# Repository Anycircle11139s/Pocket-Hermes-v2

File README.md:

# Pocket-Hermes-v2
I created a custom device which senses and displays the temperature. It is powered by a xiao esp32-s3, so it can connect to wifi/bluetooth. This can be used to fetch apis like time or bus times. I added a rotary encoder for navigation and designed it to be as compact as possible. I made the PCB black with slick af silkscreen and it is powered by a small lipo battery.

<br>

BOM: 
<br>

128 x 64 OLED display
<br>

EC11 Rotary Encoder
<br>

4.7k resistors (3)
<br>

3.7v Lipo Battery
<br>

XIAO ESP32 S3 Microcontroller
<br>

PCB
<br>

Assembly instructions:
<br>
Start by soldering all the components onto the pcb (microcontroller, OLED dislpay, temperature sensor, etc)
<br>
Next, solder the Lipo battery to the microcontroller and carefully place it in the case's slot. 
<br>
After that, screw the lid down with the m2 screws.
3D printed case from Printing Legion<br>

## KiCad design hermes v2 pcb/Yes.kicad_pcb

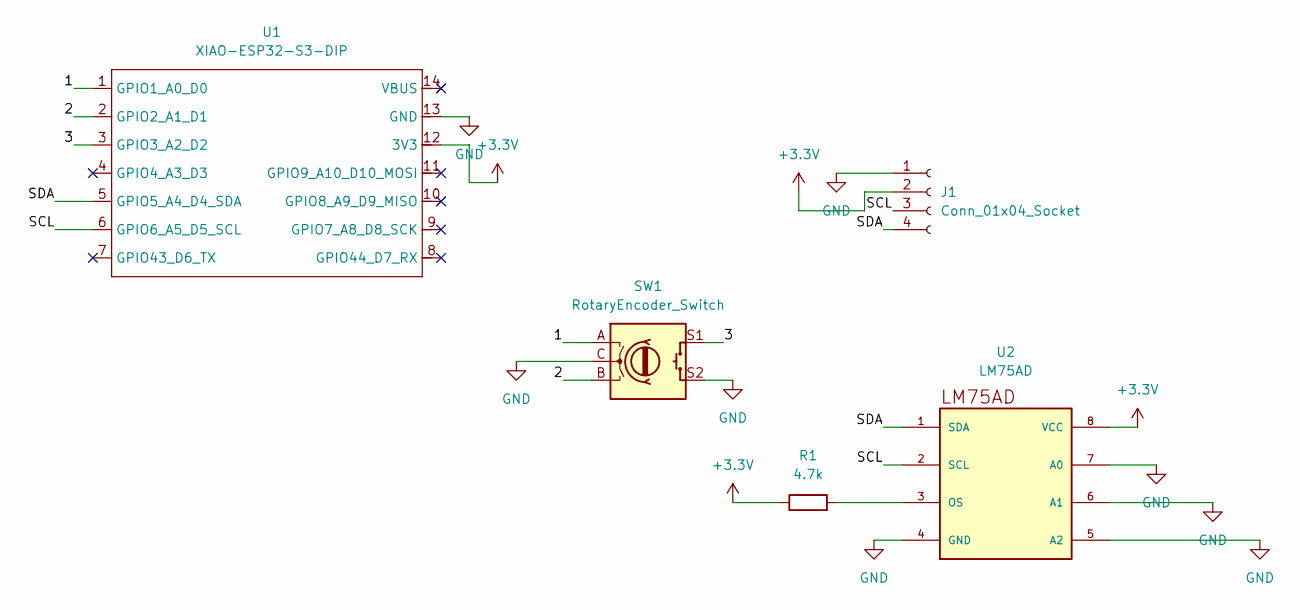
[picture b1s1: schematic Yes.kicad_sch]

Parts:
J1: Conn_01x04_Socket; PinHeader_1x04_P2.54mm_Vertical
R1: 4.7k; R_Axial_DIN0207_L6.3mm_D2.5mm_P7.62mm_Horizontal
SW1: RotaryEncoder_Switch; RotaryEncoder_Alps_EC11E-Switch_Vertical_H20mm
U1: XIAO-ESP32-S3-DIP
U2: LM75AD; SOIC-8

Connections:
+3.3V: J1.2, R1.1, U1.12 (3V3), U2.8 (VCC)
/1: SW1.A, U1.1 (GPIO1_A0_D0)
/2: SW1.B, U1.2 (GPIO2_A1_D1)
/3: SW1.S1, U1.3 (GPIO3_A2_D2)
/SCL: J1.3, U1.6 (GPIO6_A5_D5_SCL), U2.2 (SCL)
/SDA: J1.4, U1.5 (GPIO5_A4_D4_SDA), U2.1 (SDA)
GND: J1.1, SW1.C, SW1.S2, U1.13 (GND), U2.4 (GND), U2.5 (A2), U2.6 (A1), U2.7 (A0)
unnamed: R1.2, U2.3 (OS)

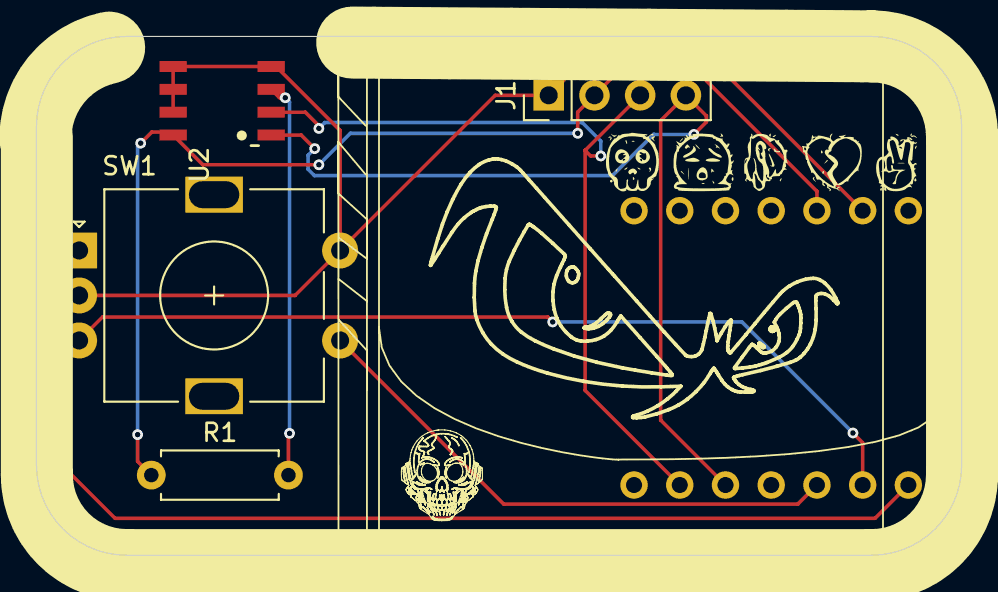
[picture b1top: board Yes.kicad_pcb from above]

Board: 2 copper layers, 51.4 x 28.8 mm, 5 parts (1 on the bottom side), 8 nets.
